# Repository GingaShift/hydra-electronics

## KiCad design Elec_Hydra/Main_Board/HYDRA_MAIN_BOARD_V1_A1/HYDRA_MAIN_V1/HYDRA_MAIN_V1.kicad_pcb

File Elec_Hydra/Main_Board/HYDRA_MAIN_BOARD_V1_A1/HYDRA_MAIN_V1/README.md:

# HYDRA MAIN BOARD V1 — A1 compacte

Projet de conception électronique du 27 octobre 2026. Ouvrir **HYDRA_MAIN_V1.kicad_pro** avec KiCad 9.0.9 ou ultérieur. Le projet est autonome : symboles et empreintes sont inclus dans `libraries`, avec tables relatives au projet. Le schéma comporte quatre feuilles. Le PCB a un contour provisoire **75 × 60 mm**, quatre couches et quatre fixations M2,5 (trous NPTH Ø2,7 mm). Le contour et les volumes connecteurs ne sont pas validés par la mécanique du ROV.

**STATUT : prototype d’ingénierie, NO-GO pour une commande de fabrication automatique.** Les fichiers sont réels; la conception et les contrôles numériques ne remplacent pas la qualification du premier matériel. Lire `docs/CHOIX_ET_VALIDATION.md`, les rapports KiCad et `docs/CONNECTEURS.md` avant toute commande. Les exports éventuels sont identifiés comme exports d’ingénierie.

## Contenu

- Schéma natif `.kicad_sch`, version PDF et PCB placé/routé `.kicad_pcb`.
- Symboles/empreintes locales, logo officiel extrait du PDF fourni.
- `docs/BOM.csv`, BOM détaillée, affectation complète des 64 broches, connectique et intégration.
- `reports/ERC.*`, `DRC.*`, `CONNECTIVITY.json` : résultats effectifs; `VALIDATION.md` donne leur interprétation.
- `previews` : vues du PCB, schéma et intégration; `fabrication` : exports réels pour revue.
- `scripts` et `design.json` : modèle de conception et génération reproductible. **Ne pas lancer les générateurs sur une version modifiée manuellement : ils reconstruisent le projet.** Les bibliothèques standards KiCad et `sexpdata` sont requis pour une reconstruction, pas pour ouvrir/utiliser le projet livré.

## Architecture

La STM32F405RGT6 surveille le BME280 interne, lit la Power Board par I2C et journalise en Flash SPI. Elle communique avec la Pi4 via le port SERIAL3 exposé par la Navigator. Aucune IMU, commande ESC, fuite, BAR30, commande Lumen ou puissance de bras/pince n’est dupliquée. Les huit broches V2 sont des signaux logiques sans drivers.

Les deux Lumen reçoivent leur énergie de la Power Board et le PWM commun de la Navigator. Aucun de ces fils ne traverse cette Main Board.

## Limites essentielles

5 V nominal uniquement; aucun raccordement au 48 V. Aucun 5 V externe sur les GPIO/ADC. Le connecteur d’extension fournit au plus 50 mA de 3,3 V au total. Alimentation et masses des cartes UART/I2C doivent suivre les règles d’intégration : débrancher les signaux vers une carte éteinte pendant les essais USB. SWD VTref est une mesure, pas une entrée d’alimentation. Ne pas alimenter le rail 3,3 V depuis un programmateur.

Le firmware applicatif et la configuration BlueOS ne font pas partie de cette livraison PCB. La programmation SWD et le démarrage du chargeur ROM USB sont prévus matériellement; leur fonctionnement sur carte assemblée n’a pas été testé.

Les modèles3D standards KiCad ne sont pas embarqués; aucune validation mécanique en3D n’est revendiquée. Les symboles et empreintes nécessaires au schéma et auPCB sont locaux.

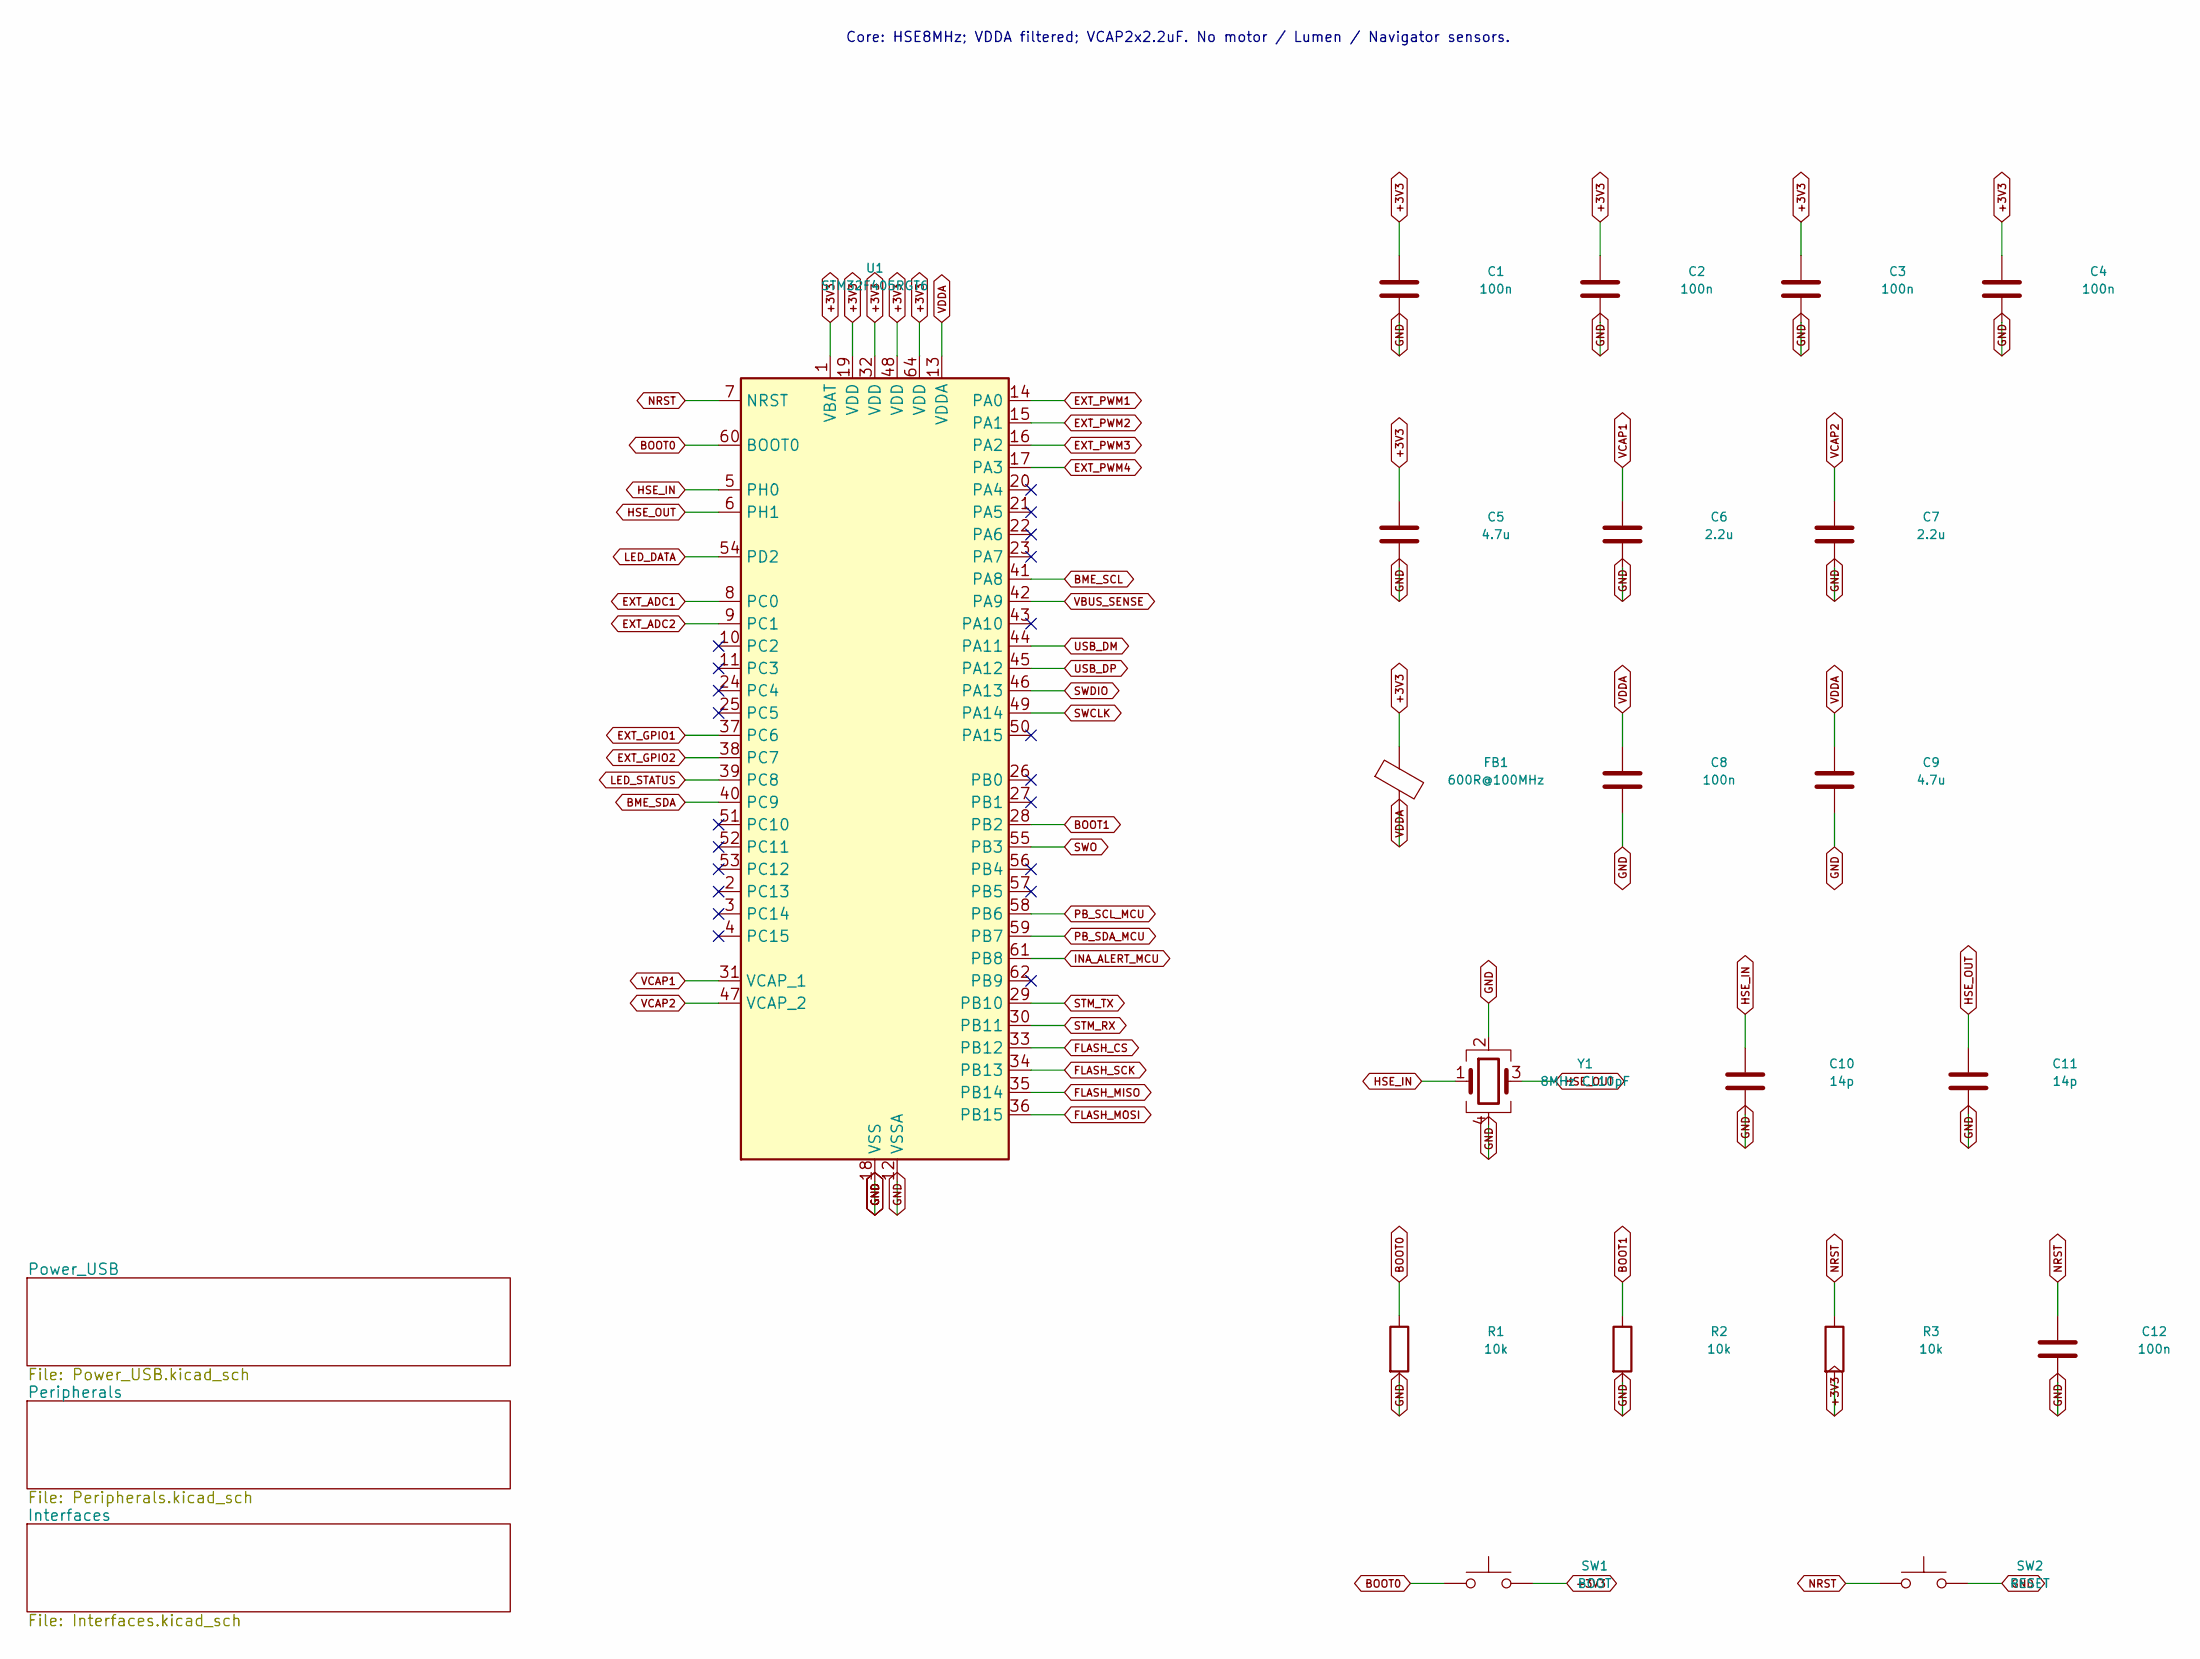
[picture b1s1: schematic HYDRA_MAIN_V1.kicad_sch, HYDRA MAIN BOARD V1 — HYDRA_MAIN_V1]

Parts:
C1, C2, C3, C4, C8, C12: 100n; C_0603_1608Metric; MPN GRM188R71C104KA01D
C5, C9: 4.7u; C_0805_2012Metric; MPN GRM21BR71A475KA73L
C6, C7: 2.2u; C_0603_1608Metric; MPN GRM188R71A225KE15D
C10, C11: 14p; C_0603_1608Metric; MPN GRM1885C1H140JA01D
FB1: 600R@100MHz; L_0603_1608Metric; MPN BLM18AG601SN1D
R1, R2, R3: 10k; R_0603_1608Metric; MPN RC0603FR-0710KL
SW1: BOOT; SW_SPST_TL3342; MPN TL3342F160QG
SW2: RESET; SW_SPST_TL3342; MPN TL3342F160QG
U1: STM32F405RGT6; LQFP-64_10x10mm_P0.5mm; MPN STM32F405RGT6
Y1: 8MHz CL10pF; Crystal_SMD_3225-4Pin_3.2x2.5mm; MPN ECS-80-10-33-CHN-TR

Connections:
+3V3: C1.1, C2.1, C3.1, C4.1, C5.1, FB1.1, R3.2, SW1.2, U1.1 (VBAT), U1.19 (VDD), U1.32 (VDD), U1.48 (VDD), U1.64 (VDD); also elsewhere on the board
BME_SCL: U1.41 (PA8); also elsewhere on the board
BME_SDA: U1.40 (PC9); also elsewhere on the board
BOOT0: R1.1, SW1.1, U1.60 (BOOT0); also elsewhere on the board
BOOT1: R2.1, U1.28 (PB2)
EXT_ADC1: U1.8 (PC0); also elsewhere on the board
EXT_ADC2: U1.9 (PC1); also elsewhere on the board
EXT_GPIO1: U1.37 (PC6); also elsewhere on the board
EXT_GPIO2: U1.38 (PC7); also elsewhere on the board
EXT_PWM1: U1.14 (PA0); also elsewhere on the board
EXT_PWM2: U1.15 (PA1); also elsewhere on the board
EXT_PWM3: U1.16 (PA2); also elsewhere on the board
EXT_PWM4: U1.17 (PA3); also elsewhere on the board
FLASH_CS: U1.33 (PB12); also elsewhere on the board
FLASH_MISO: U1.35 (PB14); also elsewhere on the board
FLASH_MOSI: U1.36 (PB15); also elsewhere on the board
FLASH_SCK: U1.34 (PB13); also elsewhere on the board
GND: C1.2, C2.2, C3.2, C4.2, C5.2, C6.2, C7.2, C8.2, C9.2, C10.2, C11.2, C12.2, R1.2, R2.2, SW2.2, U1.12 (VSSA), U1.18 (VSS), U1.63 (VSS), Y1.2, Y1.4; also elsewhere on the board
HSE_IN: C10.1, U1.5 (PH0), Y1.1
HSE_OUT: C11.1, U1.6 (PH1), Y1.3
INA_ALERT_MCU: U1.61 (PB8); also elsewhere on the board
LED_DATA: U1.54 (PD2); also elsewhere on the board
LED_STATUS: U1.39 (PC8); also elsewhere on the board
NRST: C12.1, R3.1, SW2.1, U1.7 (NRST); also elsewhere on the board
PB_SCL_MCU: U1.58 (PB6); also elsewhere on the board
PB_SDA_MCU: U1.59 (PB7); also elsewhere on the board
STM_RX: U1.30 (PB11); also elsewhere on the board
STM_TX: U1.29 (PB10); also elsewhere on the board
SWCLK: U1.49 (PA14); also elsewhere on the board
SWDIO: U1.46 (PA13); also elsewhere on the board
SWO: U1.55 (PB3); also elsewhere on the board
USB_DM: U1.44 (PA11); also elsewhere on the board
USB_DP: U1.45 (PA12); also elsewhere on the board
VBUS_SENSE: U1.42 (PA9); also elsewhere on the board
VCAP1: C6.1, U1.31 (VCAP_1)
VCAP2: C7.1, U1.47 (VCAP_2)
VDDA: C8.1, C9.1, FB1.2, U1.13 (VDDA)

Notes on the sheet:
Core: HSE8MHz; VDDA filtered; VCAP2x2.2uF. No motor / Lumen / Navigator sensors.

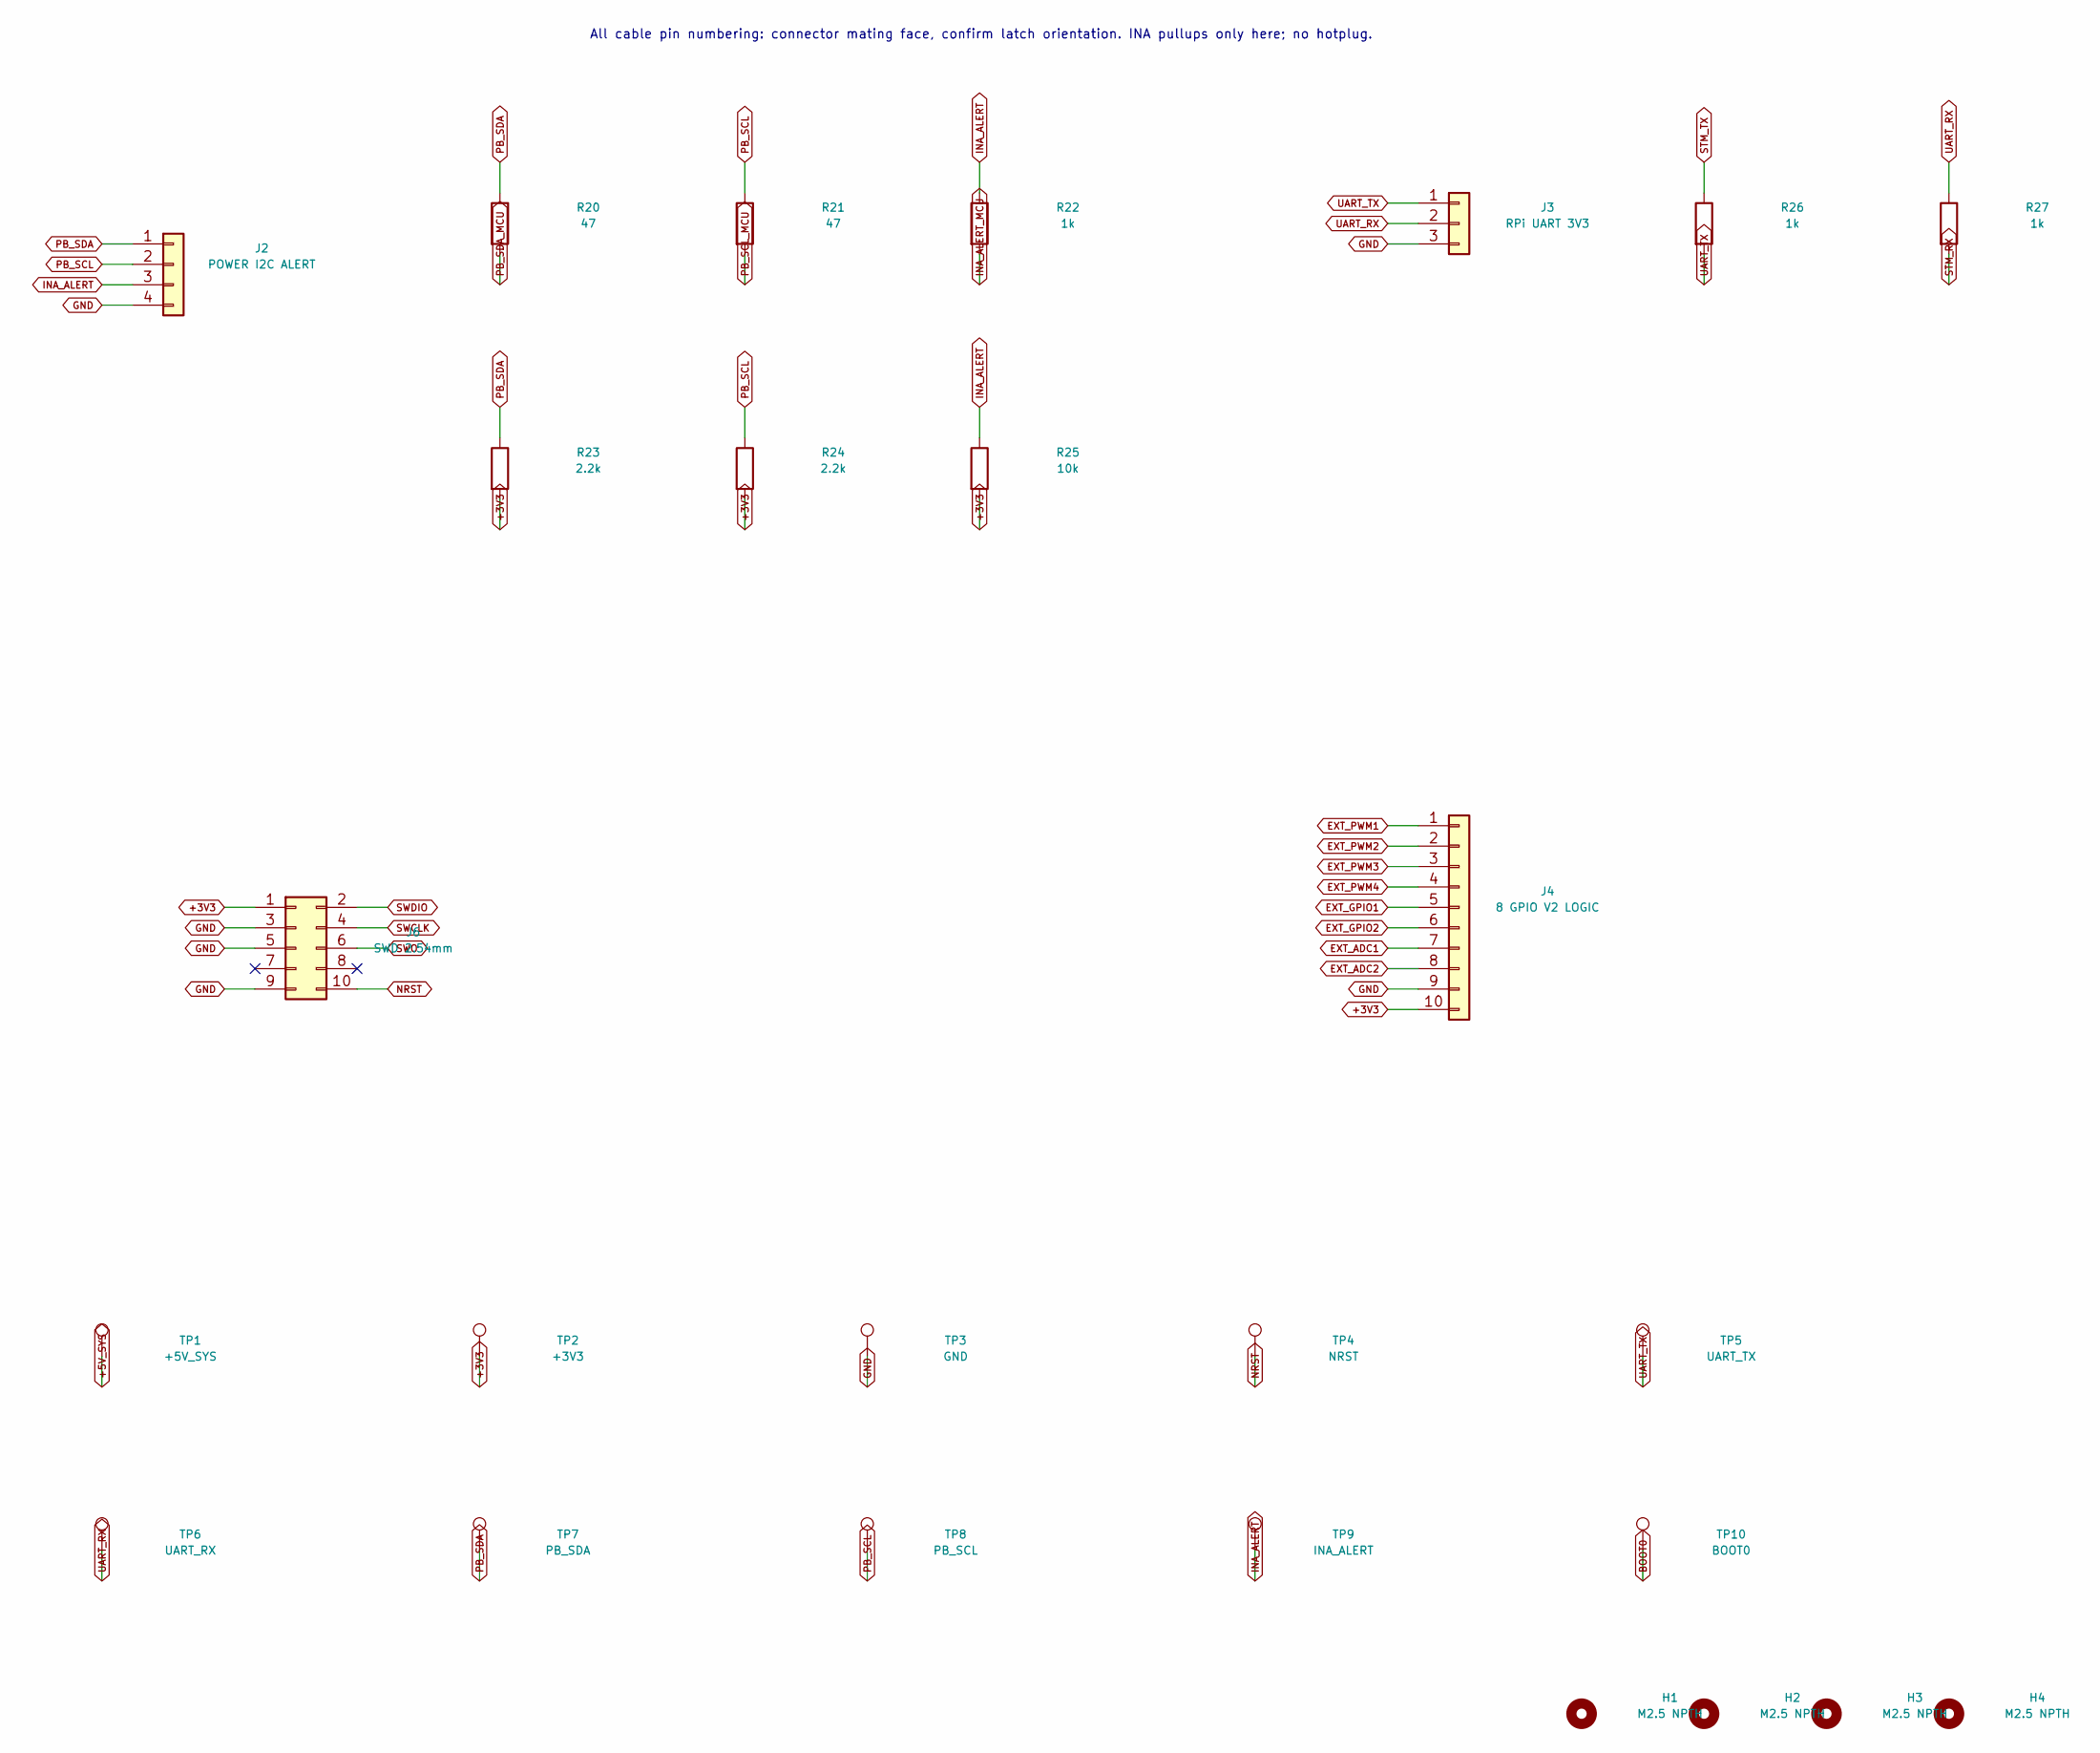
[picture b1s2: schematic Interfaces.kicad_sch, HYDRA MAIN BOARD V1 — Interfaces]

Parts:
H1, H2, H3, H4: M2.5 NPTH; MountingHole_2.7mm_M2.5
J2: POWER I2C ALERT; Molex_Micro-Latch_53253-0470_1x04_P2.00mm_Vertical; MPN 53253-0470
J3: RPi UART 3V3; Molex_Micro-Latch_53253-0370_1x03_P2.00mm_Vertical; MPN 53253-0370
J4: 8 GPIO V2 LOGIC; Molex_Micro-Latch_53253-1070_1x10_P2.00mm_Vertical; MPN 53253-1070
J6: SWD 2.54mm; PinHeader_2x05_P2.54mm_Vertical; MPN 61301021121
R20, R21: 47; R_0603_1608Metric; MPN RC0603FR-0747RL
R22, R26, R27: 1k; R_0603_1608Metric; MPN RC0603FR-071KL
R23, R24: 2.2k; R_0603_1608Metric; MPN RC0603FR-072K2L
R25: 10k; R_0603_1608Metric; MPN RC0603FR-0710KL
TP1: +5V_SYS; TestPoint_Pad_D1.5mm
TP2: +3V3; TestPoint_Pad_D1.5mm
TP3: GND; TestPoint_Pad_D1.5mm
TP4: NRST; TestPoint_Pad_D1.5mm
TP5: UART_TX; TestPoint_Pad_D1.5mm
TP6: UART_RX; TestPoint_Pad_D1.5mm
TP7: PB_SDA; TestPoint_Pad_D1.5mm
TP8: PB_SCL; TestPoint_Pad_D1.5mm
TP9: INA_ALERT; TestPoint_Pad_D1.5mm
TP10: BOOT0; TestPoint_Pad_D1.5mm

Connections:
+3V3: J4.10, J6.1, R23.2, R24.2, R25.2, TP2.1; also elsewhere on the board
+5V_SYS: TP1.1; also elsewhere on the board
BOOT0: TP10.1; also elsewhere on the board
EXT_ADC1: J4.7; also elsewhere on the board
EXT_ADC2: J4.8; also elsewhere on the board
EXT_GPIO1: J4.5; also elsewhere on the board
EXT_GPIO2: J4.6; also elsewhere on the board
EXT_PWM1: J4.1; also elsewhere on the board
EXT_PWM2: J4.2; also elsewhere on the board
EXT_PWM3: J4.3; also elsewhere on the board
EXT_PWM4: J4.4; also elsewhere on the board
GND: J2.4, J3.3, J4.9, J6.3, J6.5, J6.9, TP3.1; also elsewhere on the board
INA_ALERT: J2.3, R22.1, R25.1, TP9.1
INA_ALERT_MCU: R22.2; also elsewhere on the board
NRST: J6.10, TP4.1; also elsewhere on the board
PB_SCL: J2.2, R21.1, R24.1, TP8.1
PB_SCL_MCU: R21.2; also elsewhere on the board
PB_SDA: J2.1, R20.1, R23.1, TP7.1
PB_SDA_MCU: R20.2; also elsewhere on the board
STM_RX: R27.2; also elsewhere on the board
STM_TX: R26.1; also elsewhere on the board
SWCLK: J6.4; also elsewhere on the board
SWDIO: J6.2; also elsewhere on the board
SWO: J6.6; also elsewhere on the board
UART_RX: J3.2, R27.1, TP6.1
UART_TX: J3.1, R26.2, TP5.1

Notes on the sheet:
All cable pin numbering: connector mating face, confirm latch orientation. INA pullups only here; no hotplug.

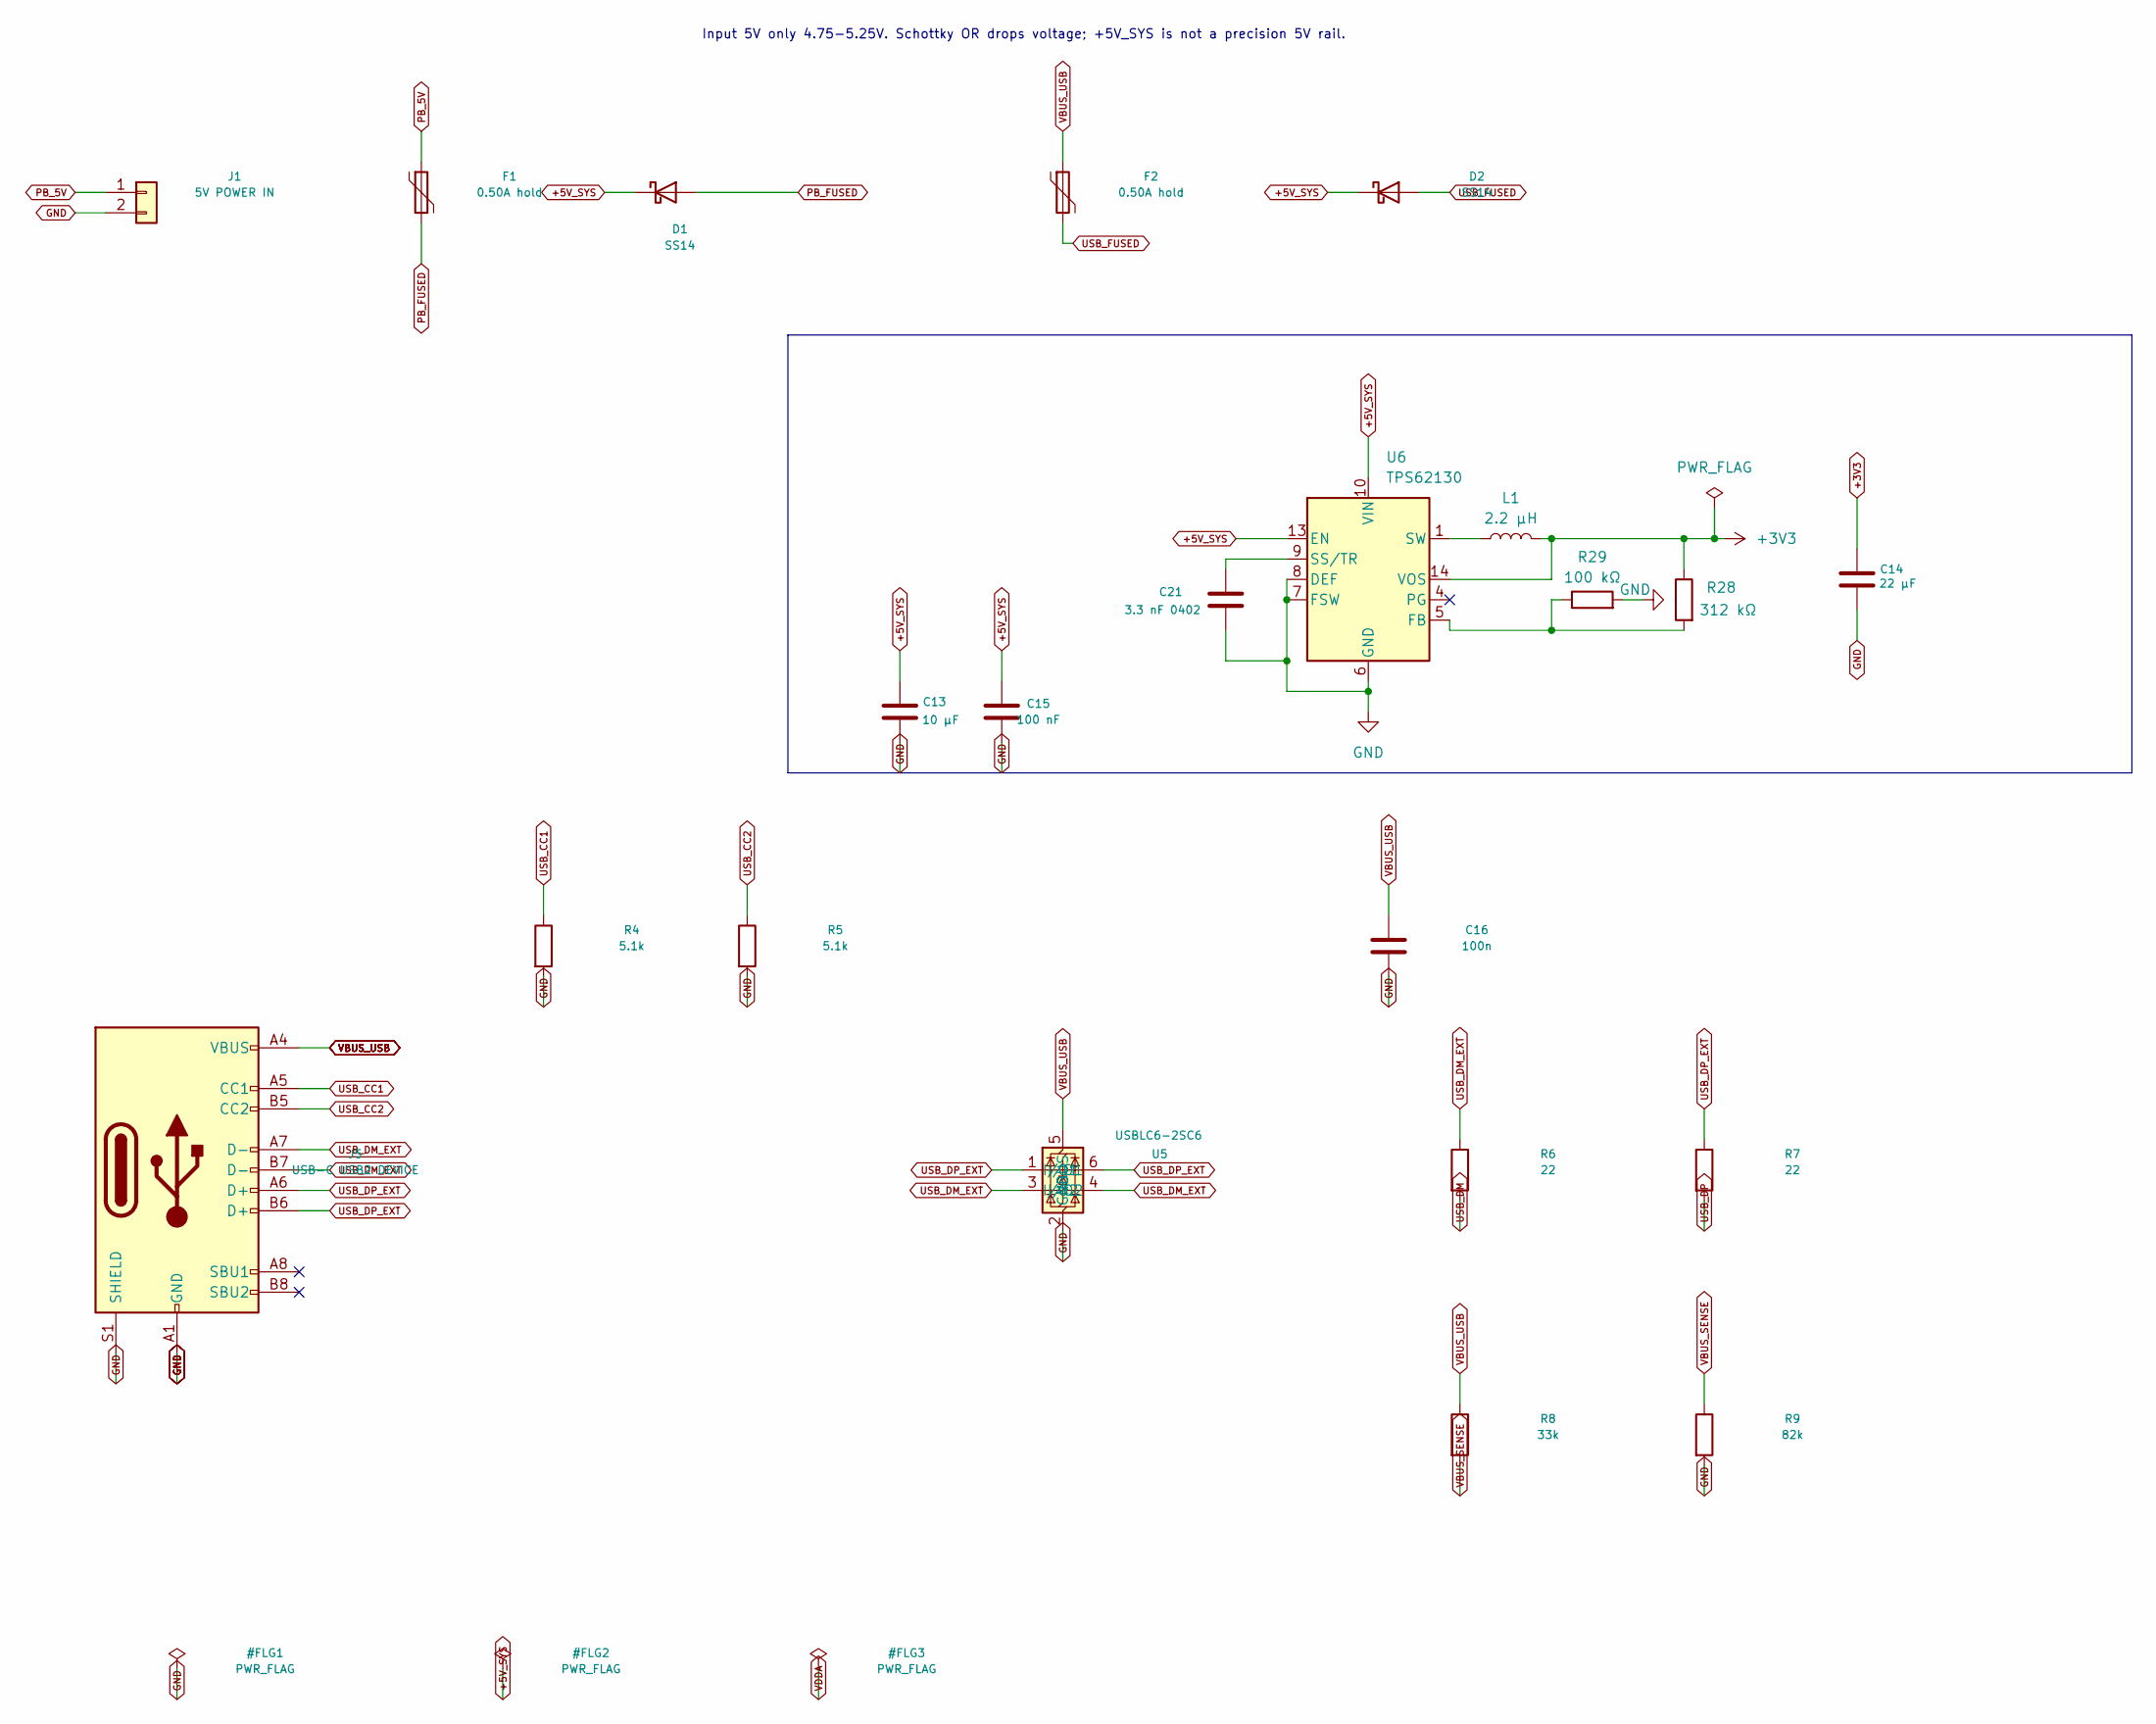
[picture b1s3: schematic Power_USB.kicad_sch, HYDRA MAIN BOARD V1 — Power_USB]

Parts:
C13: 10 µF; C_0805_2012Metric; MPN GRM21BR71A475KA73L
C14: 22 µF; C_0805_2012Metric; MPN GRM21BR71A475KA73L
C15: 100 nF; C_0603_1608Metric; MPN GRM188R71C104KA01D
C16: 100n; C_0603_1608Metric; MPN GRM188R71C104KA01D
C21: 3.3 nF 0402; C_0603_1608Metric; MPN GRM188R71C104KA01D
D1, D2: SS14; D_SMA; MPN SS14-E3/61T
F1, F2: 0.50A hold; Fuse_1206_3216Metric; MPN 1206L050/15YR
J1: 5V POWER IN; Molex_Micro-Fit_3.0_43650-0221_1x02_P3.00mm_Vertical; MPN 43650-0221
J5: USB-C USB2 DEVICE; USB_C_Receptacle_GCT_USB4105-xx-A_16P_TopMnt_Horizontal; MPN USB4105-GF-A
L1: 2.2 µH
R4, R5: 5.1k; R_0603_1608Metric; MPN RC0603FR-075K1L
R6, R7: 22; R_0603_1608Metric; MPN RC0603FR-0722RL
R8: 33k; R_0603_1608Metric; MPN RC0603FR-0733KL
R9: 82k; R_0603_1608Metric; MPN RC0603FR-0782KL
R28: 312 kΩ
R29: 100 kΩ
U5: USBLC6-2SC6; SOT-23-6; MPN USBLC6-2SC6
U6: TPS62130; VQFN-16-1EP_3x3mm_P0.5mm_EP1.68x1.68mm_ThermalVias

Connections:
+3V3: C14.1; also elsewhere on the board
+5V_SYS: C13.1, C15.1, D1.1 (K), D2.1 (K), U6.10 (VIN), U6.11 (VIN), U6.12 (VIN), U6.13 (EN); also elsewhere on the board
GND: C13.2, C14.2, C15.2, C16.2, J1.2, J5.A1 (GND), J5.A12 (GND), J5.B1 (GND), J5.B12 (GND), J5.S1 (SHIELD), R4.2, R5.2, R9.2, U5.2 (GND); also elsewhere on the board
unnamed: C21.1, U6.9 (SS/TR)
unnamed: C21.2, R29.2, U6.6 (GND), U6.7 (FSW), U6.8 (DEF), U6.15 (GND), U6.16 (GND), U6.17 (GND)
unnamed: L1.1, U6.1 (SW), U6.2 (SW), U6.3 (SW)
unnamed: L1.2, R28.1, U6.14 (VOS)
unnamed: R28.2, R29.1, U6.5 (FB)
PB_5V: F1.1, J1.1
PB_FUSED: D1.2 (A), F1.2
USB_CC1: J5.A5 (CC1), R4.1
USB_CC2: J5.B5 (CC2), R5.1
USB_DM: R6.2; also elsewhere on the board
USB_DM_EXT: J5.A7 (D-), J5.B7 (D-), R6.1, U5.3 (I/O2), U5.4 (I/O2)
USB_DP: R7.2; also elsewhere on the board
USB_DP_EXT: J5.A6 (D+), J5.B6 (D+), R7.1, U5.1 (I/O1), U5.6 (I/O1)
USB_FUSED: D2.2 (A), F2.2
VBUS_SENSE: R8.2, R9.1; also elsewhere on the board
VBUS_USB: C16.1, F2.1, J5.A4 (VBUS), J5.A9 (VBUS), J5.B4 (VBUS), J5.B9 (VBUS), R8.1, U5.5 (VBUS)

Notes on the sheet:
Input 5V only 4.75-5.25V. Schottky OR drops voltage; +5V_SYS is not a precision 5V rail.

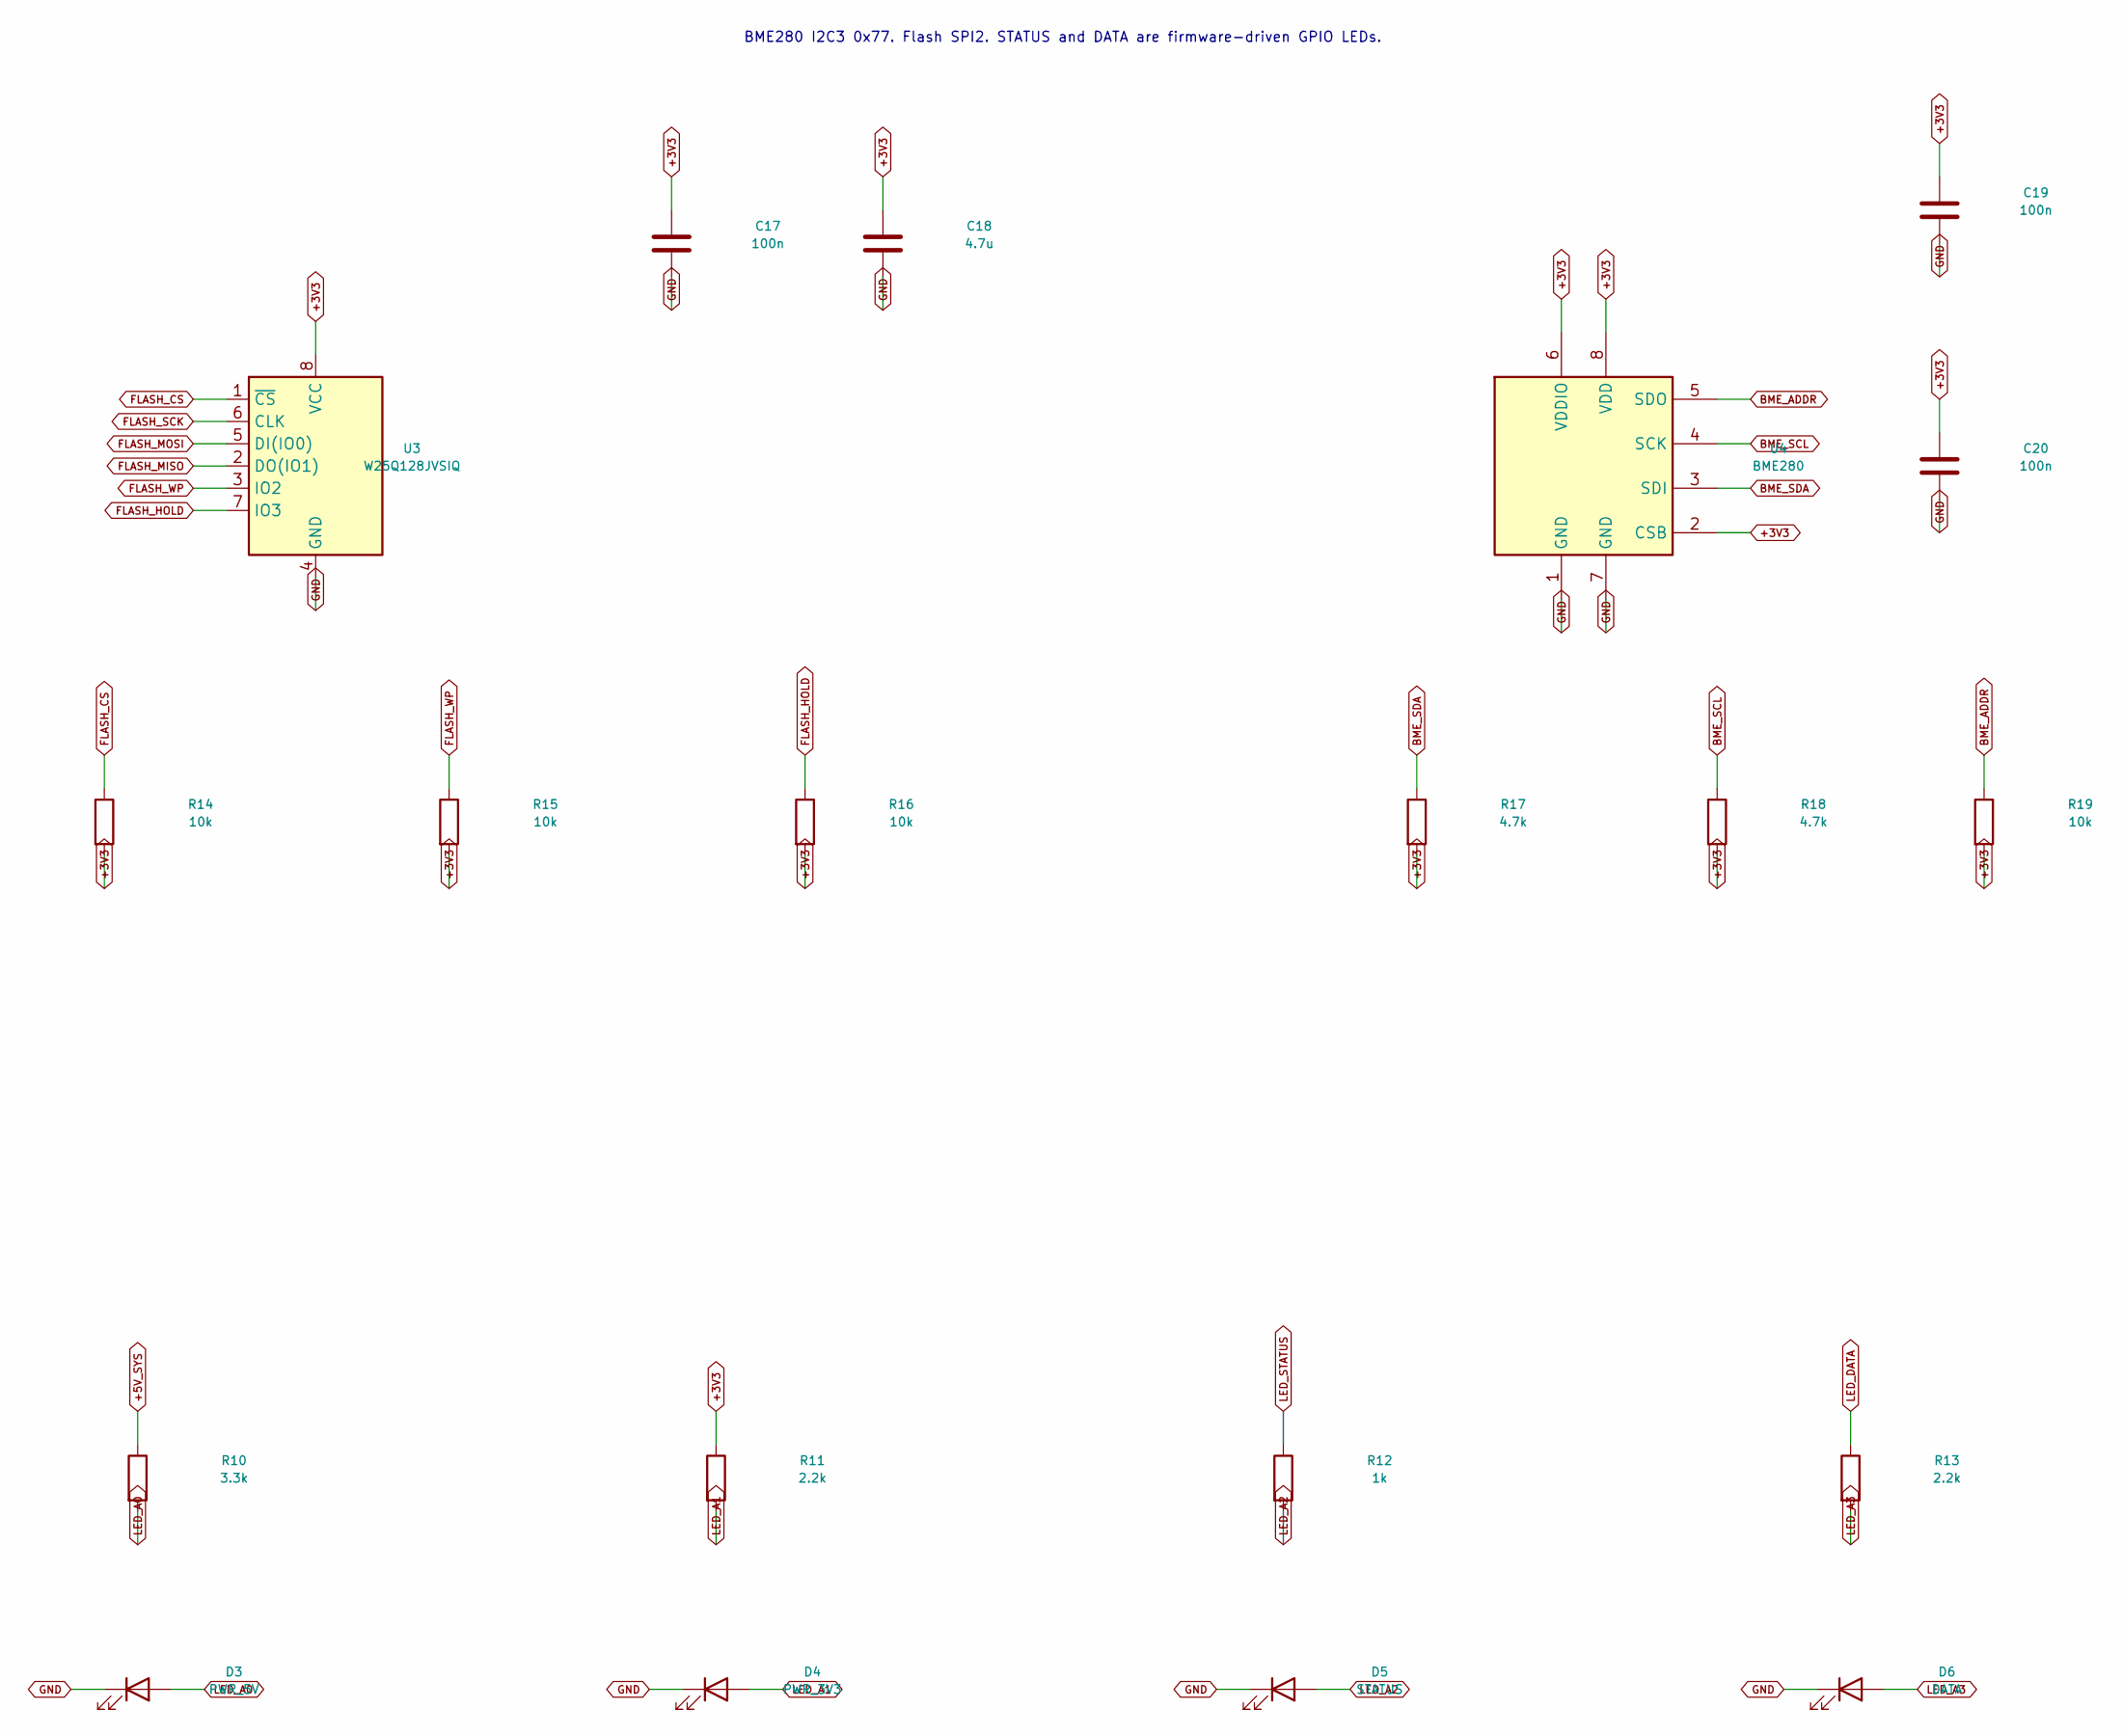
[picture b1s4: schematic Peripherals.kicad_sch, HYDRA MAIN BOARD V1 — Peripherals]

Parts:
C17, C19, C20: 100n; C_0603_1608Metric; MPN GRM188R71C104KA01D
C18: 4.7u; C_0805_2012Metric; MPN GRM21BR71A475KA73L
D3: PWR_5V; LED_0603_1608Metric; MPN LTST-C190KGKT
D4: PWR_3V3; LED_0603_1608Metric; MPN LTST-C190KGKT
D5: STATUS; LED_0603_1608Metric; MPN LTST-C190TBKT
D6: DATA; LED_0603_1608Metric; MPN LTST-C190KSKT
R10: 3.3k; R_0603_1608Metric; MPN RC0603FR-073K3L
R11, R13: 2.2k; R_0603_1608Metric; MPN RC0603FR-072K2L
R12: 1k; R_0603_1608Metric; MPN RC0603FR-071KL
R14, R15, R16, R19: 10k; R_0603_1608Metric; MPN RC0603FR-0710KL
R17, R18: 4.7k; R_0603_1608Metric; MPN RC0603FR-074K7L
U3: W25Q128JVSIQ; SOIC-8_5.23x5.23mm_P1.27mm; MPN W25Q128JVSIQ
U4: BME280; Bosch_LGA-8_2.5x2.5mm_P0.65mm_ClockwisePinNumbering; MPN BME280

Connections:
+3V3: C17.1, C18.1, C19.1, C20.1, R11.1, R14.2, R15.2, R16.2, R17.2, R18.2, R19.2, U3.8 (VCC), U4.2 (CSB), U4.6 (VDDIO), U4.8 (VDD); also elsewhere on the board
+5V_SYS: R10.1; also elsewhere on the board
BME_ADDR: R19.1, U4.5 (SDO)
BME_SCL: R18.1, U4.4 (SCK); also elsewhere on the board
BME_SDA: R17.1, U4.3 (SDI); also elsewhere on the board
FLASH_CS: R14.1, U3.1 (~CS); also elsewhere on the board
FLASH_HOLD: R16.1, U3.7 (IO3)
FLASH_MISO: U3.2 (DO(IO1)); also elsewhere on the board
FLASH_MOSI: U3.5 (DI(IO0)); also elsewhere on the board
FLASH_SCK: U3.6 (CLK); also elsewhere on the board
FLASH_WP: R15.1, U3.3 (IO2)
GND: C17.2, C18.2, C19.2, C20.2, D3.1 (K), D4.1 (K), D5.1 (K), D6.1 (K), U3.4 (GND), U4.1 (GND), U4.7 (GND); also elsewhere on the board
LED_A0: D3.2 (A), R10.2
LED_A1: D4.2 (A), R11.2
LED_A2: D5.2 (A), R12.2
LED_A3: D6.2 (A), R13.2
LED_DATA: R13.1; also elsewhere on the board
LED_STATUS: R12.1; also elsewhere on the board

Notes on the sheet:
BME280 I2C3 0x77. Flash SPI2. STATUS and DATA are firmware-driven GPIO LEDs.
